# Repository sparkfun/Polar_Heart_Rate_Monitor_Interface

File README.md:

SparkFun Polar Heart Rate Monitor Interface
========================================

[*SparkFun Polar Heart Rate Monitor Interface (SEN-08661)*](https://www.sparkfun.com/products/8661)

The Heart Rate Monitor Interface (HRMI) is an intelligent peripheral device that converts the ECG signal from the Polar Heart Rate Monitor (HRM) 
into easy-to-use heart rate data.

Repository Contents
-------------------
* **/Hardware** - All Eagle design files (.brd, .sch)

License Information
-------------------
The hardware is released under [Creative Commons ShareAlike 4.0 International](https://creativecommons.org/licenses/by-sa/4.0/).

This product is a collaboration with Dan Julio. A portion of each sales goes back to them for product support and continued development.

Distributed as-is; no warranty is given.

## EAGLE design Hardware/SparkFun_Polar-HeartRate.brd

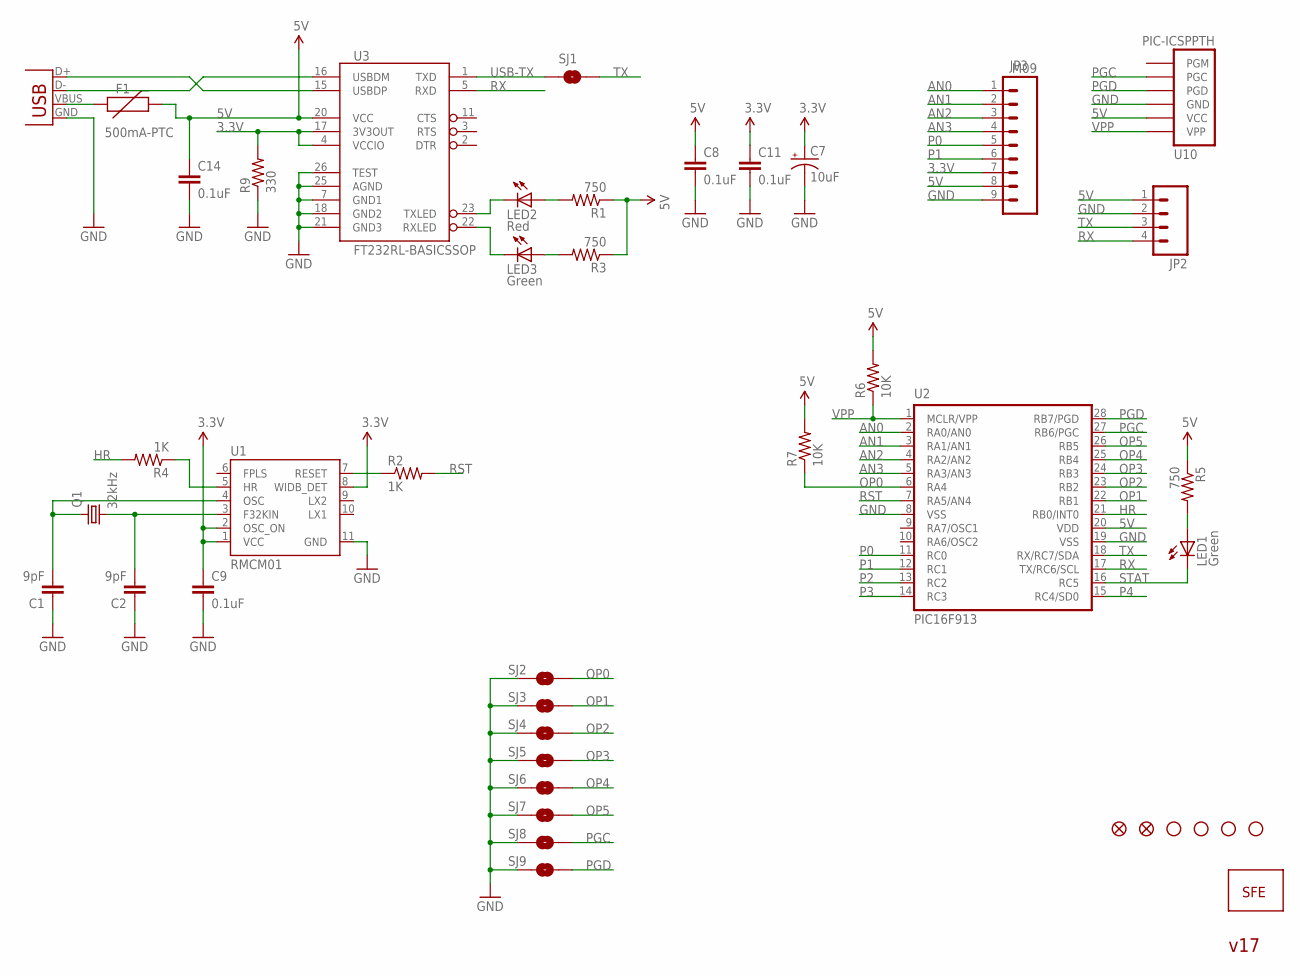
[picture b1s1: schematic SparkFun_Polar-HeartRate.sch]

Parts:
C1, C2: 9pF; 0402-CAP
C7: 10uF; EIA3216
C8, C9, C11, C14: 0.1uF; 0402-CAP
F1: 500mA-PTC; PTC-1206
JP2: M04PTH; 1X04
JP3: M09; 1X09
LED1, LED3: Green; LED-0603
LED2: Red; LED-0603
Q1: 32kHz; CRYSTAL-32KHZ-SMD_EPSON_MC146
R1, R3, R5: 750; 0402-RES
R2, R4: 1K; 0402-RES
R6, R7: 10K; 0402-RES
R9: 330; 0402-RES
SJ1: SOLDERJUMPERNC2; SJ_2S-NOTRACE
SJ2, SJ3, SJ4, SJ5, SJ6, SJ7, SJ8, SJ9: SOLDERJUMPERNO; SJ_2S-NO
U1: RMCM01
U2: PIC16F913; SO-28W
U3: FT232RL-BASICSSOP; SSOP28DB
U10: PIC-ICSPPTH; MOLEX-1X6
U$1: LOGO-SFENEW; SFE-NEW-WEBLOGO
U$4, U$8: FIDUCIAL1X2; FIDUCIAL-1X2
U$13, U$15, U$16, U$17: STAND-OFF
X1: USBSMD; USB-MINIB

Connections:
3.3V: C7.A (+), C9.1, C11.1, JP3.7, R9.2, U1.1 (VCC), U1.2 (OSC_ON), U1.8 (WIDB_DET), U3.4 (VCCIO), U3.17 (3V3OUT)
5V: C8.1, C14.1, F1.2, JP2.1, JP3.8, R1.1, R3.1, R5.1, R6.2, R7.2, U2.20 (VDD), U3.20 (VCC), U10.5 (VCC)
AN0: JP3.1, U2.2 (RA0/AN0)
AN1: JP3.2, U2.3 (RA1/AN1)
AN2: JP3.3, U2.4 (RA2/AN2)
AN3: JP3.4, U2.5 (RA3/AN3)
GND: C1.1, C2.1, C7.C (-), C8.2, C9.2, C11.2, C14.2, JP2.2, JP3.9, R9.1, SJ2.1, SJ3.1, SJ4.1, SJ5.1, SJ6.1, SJ7.1, SJ8.1, SJ9.1, U1.11 (GND), U2.8 (VSS), U2.19 (VSS), U3.7 (GND1), U3.18 (GND2), U3.21 (GND3), U3.25 (AGND), U3.26 (TEST), U10.4 (GND), X1.GND
HR: R4.2, U2.21 (RB0/INT0)
unnamed: LED2.A, R1.2
unnamed: U3.16 (USBDM), X1.D-
unnamed: LED3.A, R3.2
unnamed: U3.15 (USBDP), X1.D+
unnamed: LED1.A, R5.2
unnamed: R4.1, U1.5 (HR)
unnamed: R2.1, U1.7 (RESET)
unnamed: C1.2, Q1.P$1 (2), U1.4 (OSC)
unnamed: C2.2, Q1.P$2 (1), U1.3 (F32KIN)
OP0: R7.1, SJ2.2, U2.6 (RA4)
OP1: SJ3.2, U2.22 (RB1)
OP2: SJ4.2, U2.23 (RB2)
OP3: SJ5.2, U2.24 (RB3)
OP4: SJ6.2, U2.25 (RB4)
OP5: SJ7.2, U2.26 (RB5)
P0: JP3.5, U2.11 (RC0)
P1: JP3.6, U2.12 (RC1)
P2: U2.13 (RC2)
P3: U2.14 (RC3)
P4: U2.15 (RC4/SD0)
PGC: SJ8.2, U2.27 (RB6/PGC), U10.2 (PGC)
PGD: SJ9.2, U2.28 (RB7/PGD), U10.3 (PGD)
RST: R2.2, U2.7 (RA5/AN4)
RX: JP2.4, U2.17 (TX/RC6/SCL), U3.5 (RXD)
RXLED: LED3.C, U3.22 (RXLED)
STAT: LED1.C, U2.16 (RC5)
TX: JP2.3, SJ1.2, U2.18 (RX/RC7/SDA)
TXLED: LED2.C, U3.23 (TXLED)
USB-TX: SJ1.1, U3.1 (TXD)
VBUS: F1.1, X1.VBUS
VPP: R6.1, U2.1 (MCLR/VPP), U10.6 (VPP)

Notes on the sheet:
v17

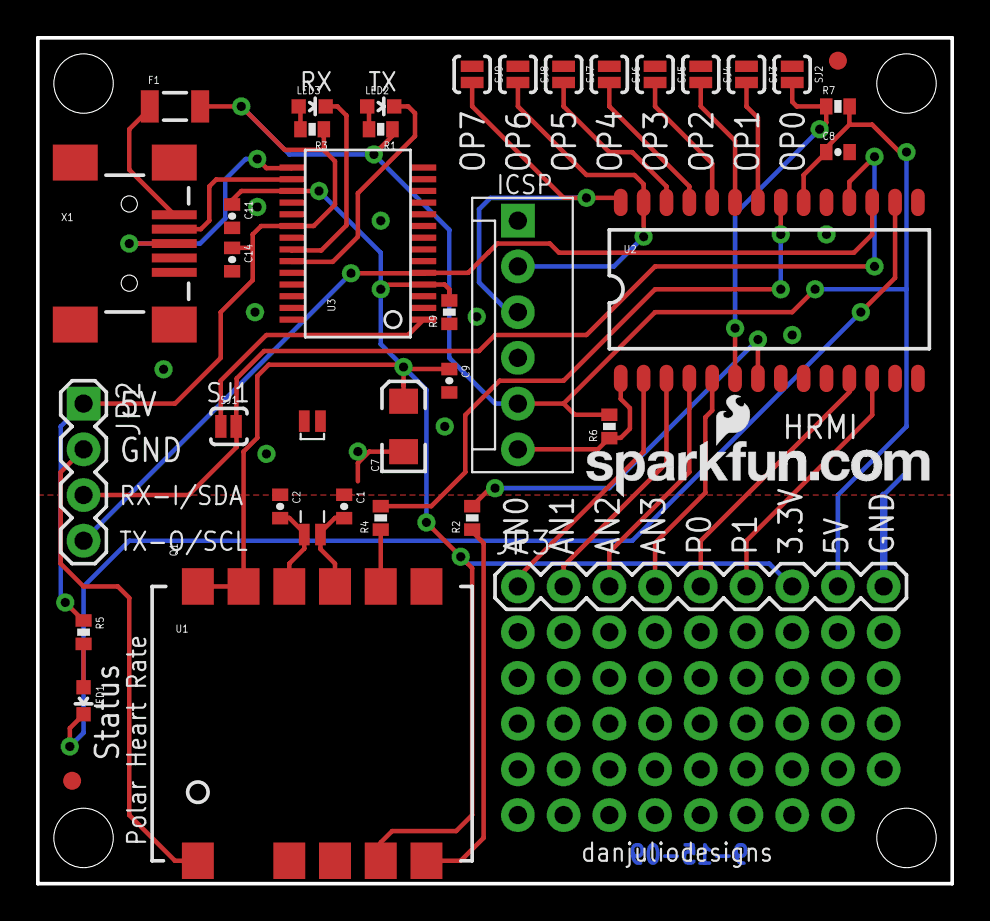
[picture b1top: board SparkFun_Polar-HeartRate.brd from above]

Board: 2 copper layers, 50.8 x 47.0 mm, 43 parts (0 on the bottom side), 36 nets.

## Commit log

2015-01-29 Initial hardware commit
